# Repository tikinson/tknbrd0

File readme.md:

# tknbrd0

## Intro
### ( !ACHTUNG! work in progress, use by your own risk! )

After a couple of sleepless nights, I decided to get my hands dirty with this sweet and diverse world of mechanical keyboards. As i understood on my way to my current daily driver it's quite interesting challenge. My main idea was to make a cheap keyboard, that can guide me forward in this hobby. 

So, i made a rough sketch of the location of my fingers to understand how far i must go with [ergogen](https://ergogen.xyz/) and then use spacing of switches in KiCad to make a PCB. Also this isn't a bad idea to play around with encoders and small OLED display in my project. As it usually almost everytime happens with first try, i made some mistakes ( learned some lessons :D ) and realize this _after_ i got PCBs from manufacturer. It's not critical, but in some points it could be just unexpectable for those, who would repeat my project. 

By the way here is PCBs appearance:

 WPM and remix of [bongo cat animation](https://www.reddit.com/r/olkb/comments/h00a8b/i_made_an_oled_animation_of_bongo_cat_that/) is showing on my OLED (of course with picture of my cat instead of original one!). With encoders i can scroll my feed, and also fast forward/backward the YouTube videos by 5 seconds. Encoders is very interesting feature in keyboards and detailed explanation of this you can check in [QMK Docs](https://docs.qmk.fm/features/encoders).

 #### important note: in first version of my schematics, unfortunately, encoders works not so stable as expected... sometimes for correct working keyboard must be rebooted.

## Keymap

My keyboard has a 42 keys, and it planned to use with QWERTY layout. For me is also iportant to have access to ukrainian letter Ґ, Ї, and some umlaut letters
Ä, Ö, Ü. I have now a laptop with QWERTZ layout, so have a keyboard with comfortable QWERTY is must have for me. So here is the keymap:

## Case

In file 'path_for400x300.svg' in this repo you can find a complete graphical outline for lasercutted case. I used a 3 mm acrylic sheet and laser in local FabLab.

## Firmware 

I created a fork of QMK firmware [here](https://github.com/tikinson/qmk_firmware) and [here](https://github.com/tikinson/qmk_firmware/tree/master/keyboards/tknbrd/tknbrd0) is tknbrd0 is located inside of QMK fork.

So you can compile firmware from fork or you can find binaries in 'FW' directory of this repo.

## Some important notes

1. Footprint for OLED is mirrored, so i use wires and simple pair of acrylic pieces to hold it with glue (really not a clearest design decision, but it just a first experience, so when it works it works).
2. Case: it's very important to solder RPI Pico a bit higher that it could be to prevent collision with acrylic case!!!
3. Encoders may have strange behaviour because they are connected to one pin. it was a bad decision and when reset keyboard isn't working i just rotate them together for first and then separately, so after this magical manipulation they works as usual.

## BOM (Bill of materials)

Interactive BOM could be handy in assembling process and you can find it [here](/bom/ibom.html)

| Designator       | Footprint                                                        | Quantity | Value                 | LCSC Part #      |
|------------------|------------------------------------------------------------------|----------|-----------------------|------------------|
| D1 - D42         | Diode_SOD-123                                                   | 42       | Diode                 |C83528              |
| EXSW1, EXSW2     | RotaryEncoder_Alps_EC11E-Switch_Vertical_H20mm_CircularMountingHoles | 2        | RotaryEncoder_Switch   |C1322543         |
| J1               | OLED_128x64 (I2C version)                                       | 1        | Conn_01x04            |                  |
| S1 - S42         | MX_PCB_1.00u                                                    | 42       | Keyswitch             |                  |
| U1               | Raspberry_Pi_Pico                                               | 1        | Raspberry_Pi_Pico     |                  |
| rD1              | D_SOD-523                                                       | 1        | 1N4148WT              | C232841          |
| rLED1 - rLED42    | YS-SK6812MINI-E-withCUTOUT                                     | 42       | YS-SK6812MINI-E       |C5149201          |
| aluminum spacer M2(standoff)    |MountingHole_4.3mm_M4_ISO14580                    | 8        | standoff              |                  |

Lasercutting, Knob, Switches all this you can easily find on market on your personal preferences. All that included in BOM is recommended, only LED is optional.

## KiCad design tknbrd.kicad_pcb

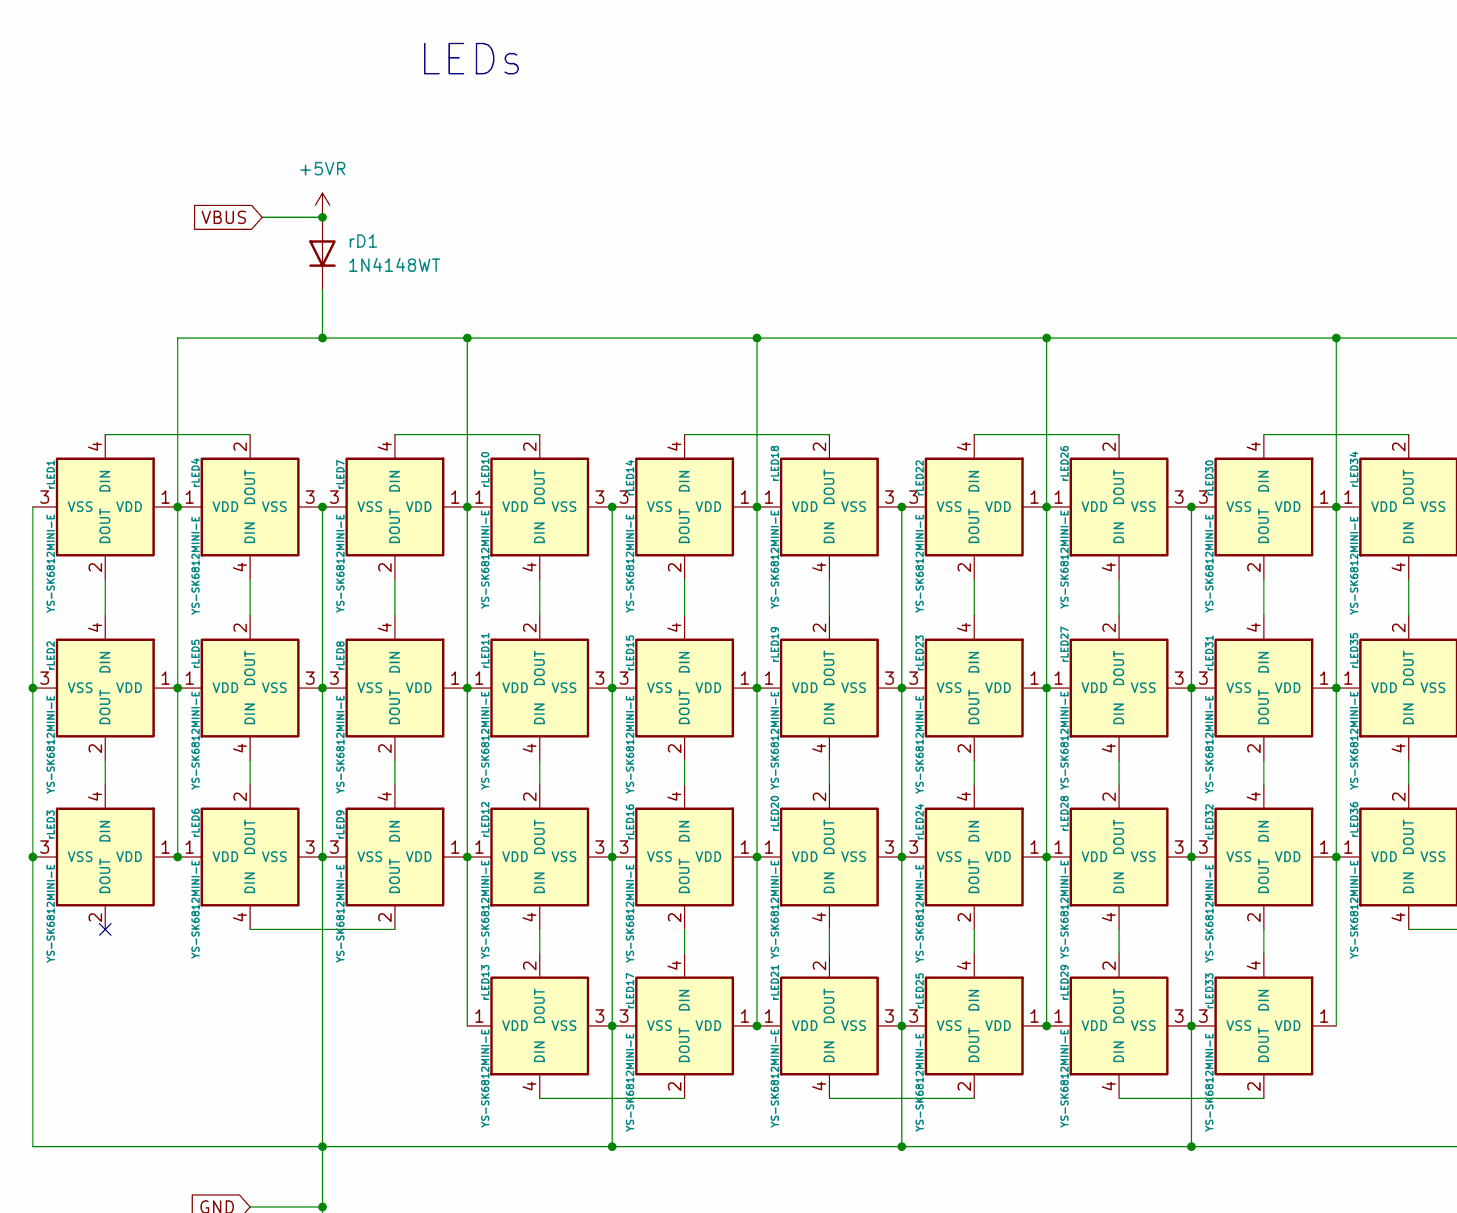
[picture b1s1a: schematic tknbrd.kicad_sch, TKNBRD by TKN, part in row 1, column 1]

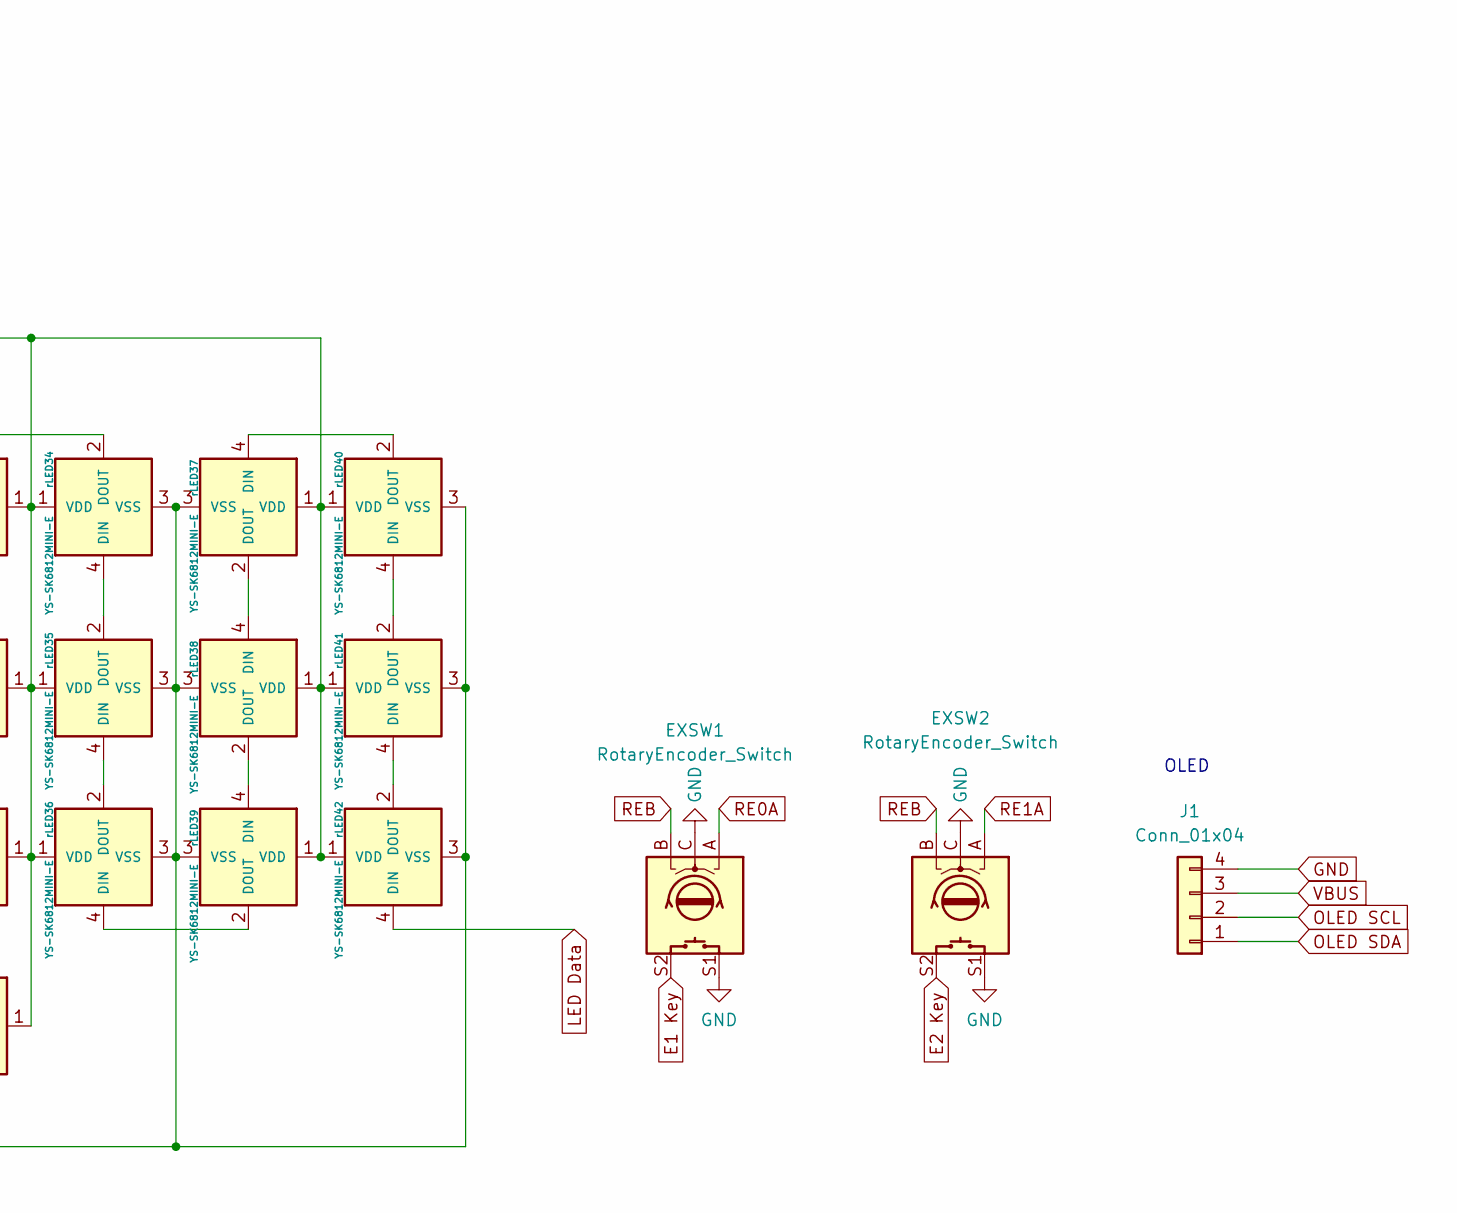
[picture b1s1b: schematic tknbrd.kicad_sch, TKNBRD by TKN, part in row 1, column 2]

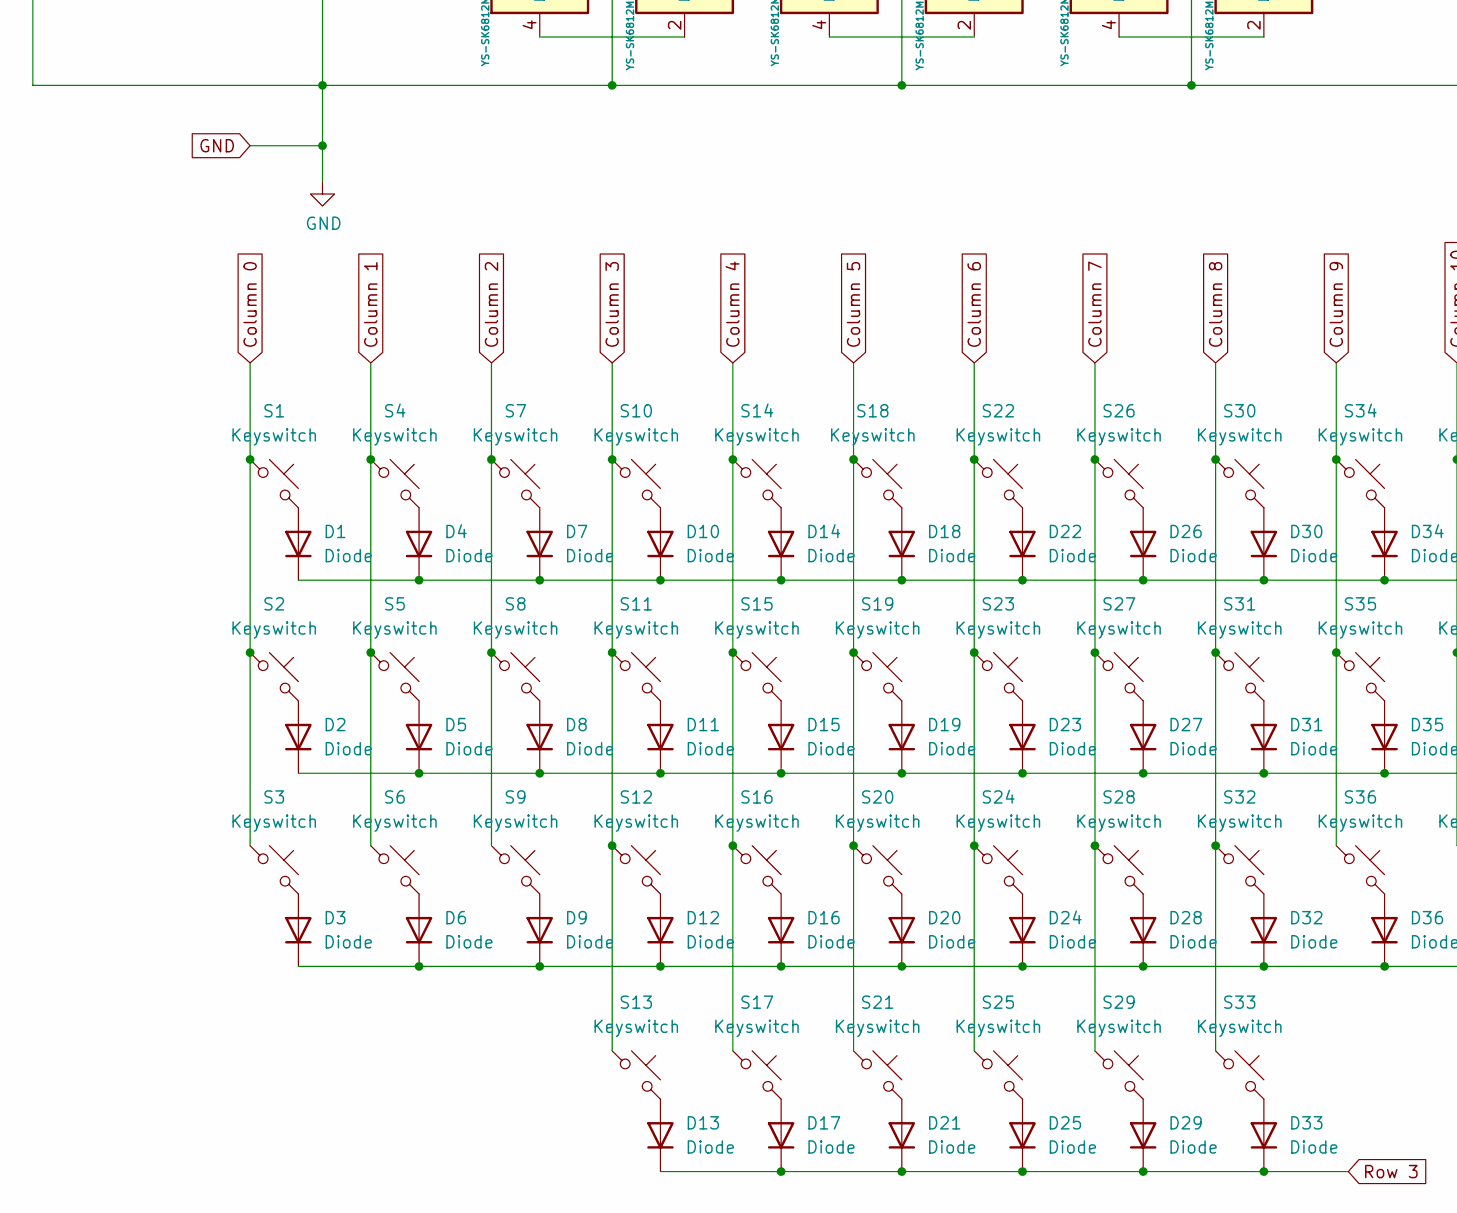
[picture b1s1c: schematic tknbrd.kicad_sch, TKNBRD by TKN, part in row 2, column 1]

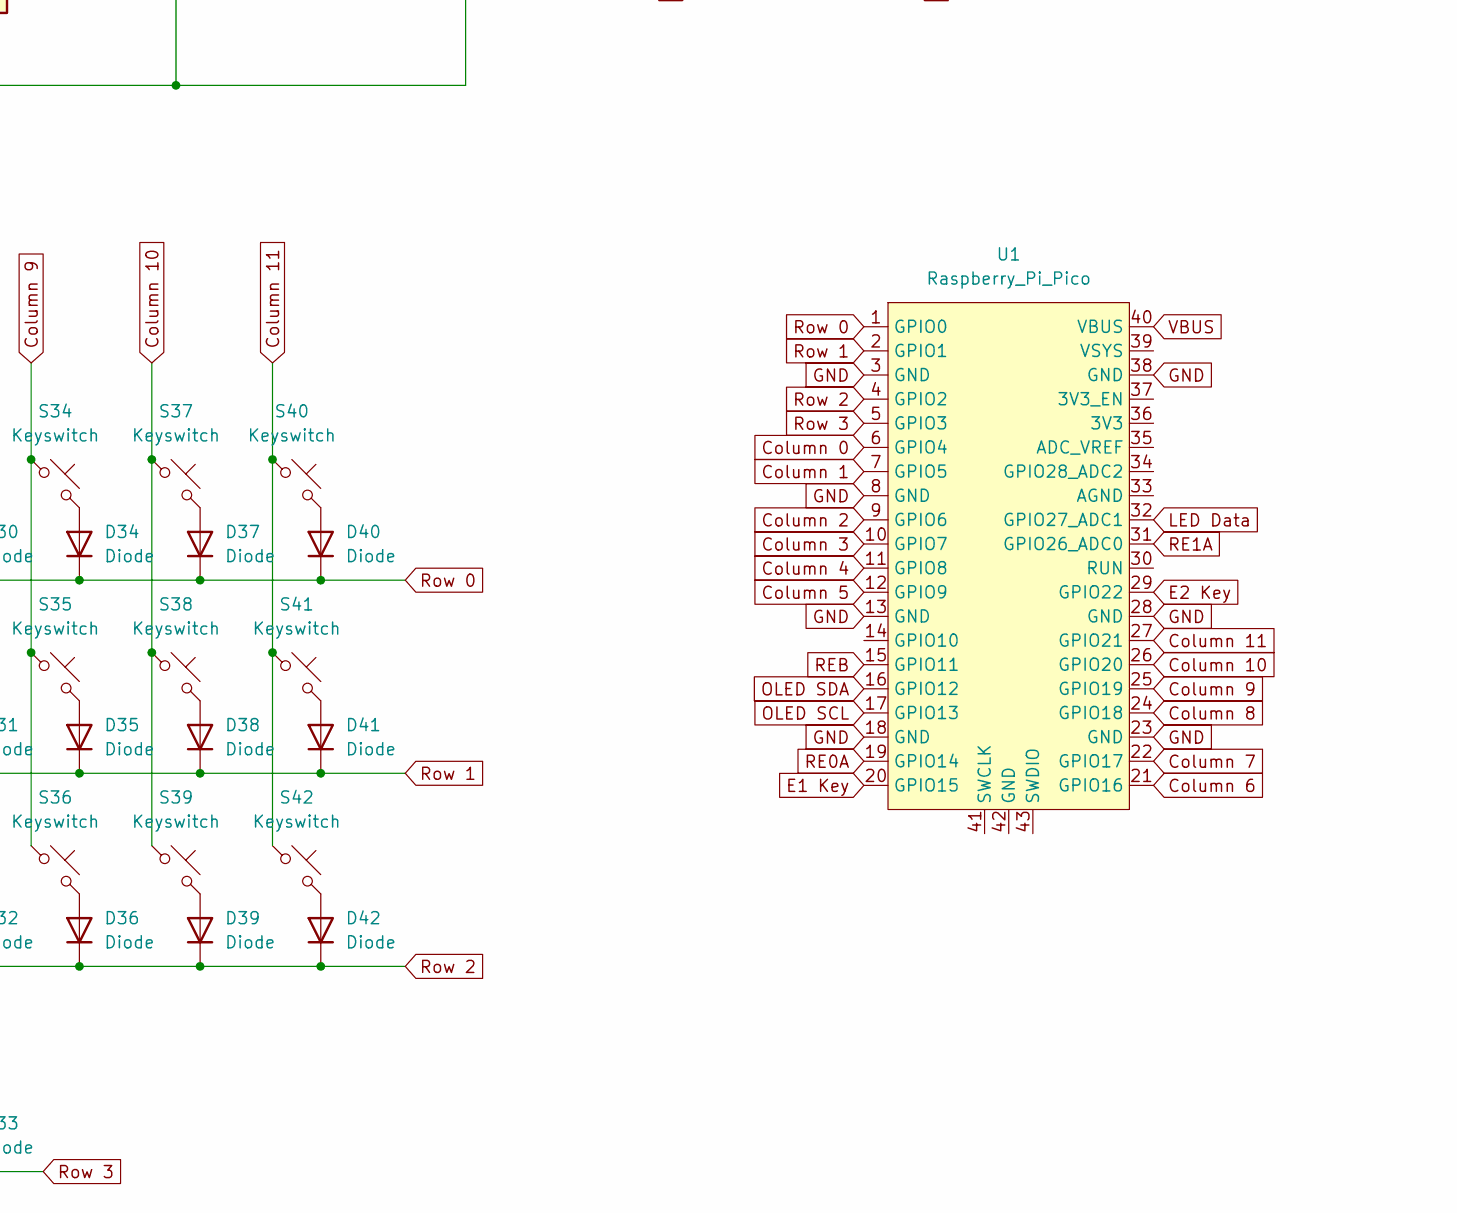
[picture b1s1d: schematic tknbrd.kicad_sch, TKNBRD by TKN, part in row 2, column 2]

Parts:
D1, D2, D3, D4, D5, D6, D7, D8, D9, D10, D11, D12, D13, D14, D15, D16, D17, D18, D19, D20, D21, D22, D23, D24, D25, D26, D27, D28, D29, D30, D31, D32, D33, D34, D35, D36, D37, D38, D39, D40, D41, D42: Diode; Diode_SOD-123
EXSW1, EXSW2: RotaryEncoder_Switch; RotaryEncoder_Alps_EC11E-Switch_Vertical_H20mm_CircularMoun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
J1: Conn_01x04; OLED_128x64
S1, S2, S3, S4, S5, S6, S7, S8, S9, S10, S11, S12, S13, S14, S15, S16, S17, S18, S19, S20, S21, S22, S23, S24, S25, S26, S27, S28, S29, S30, S31, S32, S33, S34, S35, S36, S37, S38, S39, S40, S41, S42: Keyswitch; MX_PCB_1.00u
U1: Raspberry_Pi_Pico
rD1: 1N4148WT; D_SOD-523; JLCPCB Part # C232841
rLED1, rLED2, rLED3, rLED4, rLED5, rLED6, rLED7, rLED8, rLED9, rLED10, rLED11, rLED12, rLED13, rLED14, rLED15, rLED16, rLED17, rLED18, rLED19, rLED20, rLED21, rLED22, rLED23, rLED24, rLED25, rLED26, rLED27, rLED28, rLED29, rLED30, rLED31, rLED32, rLED33, rLED34, rLED35, rLED36, rLED37, rLED38, rLED39, rLED40, rLED41, rLED42: YS-SK6812MINI-E; YS-SK6812MINI-E-withCUTOUT

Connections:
Column 0: S1.1, S2.1, S3.1, U1.6 (GPIO4)
Column 1: S4.1, S5.1, S6.1, U1.7 (GPIO5)
Column 2: S7.1, S8.1, S9.1, U1.9 (GPIO6)
Column 3: S10.1, S11.1, S12.1, S13.1, U1.10 (GPIO7)
Column 4: S14.1, S15.1, S16.1, S17.1, U1.11 (GPIO8)
Column 5: S18.1, S19.1, S20.1, S21.1, U1.12 (GPIO9)
Column 6: S22.1, S23.1, S24.1, S25.1, U1.21 (GPIO16)
Column 7: S26.1, S27.1, S28.1, S29.1, U1.22 (GPIO17)
Column 8: S30.1, S31.1, S32.1, S33.1, U1.24 (GPIO18)
Column 9: S34.1, S35.1, S36.1, U1.25 (GPIO19)
Column 10: S37.1, S38.1, S39.1, U1.26 (GPIO20)
Column 11: S40.1, S41.1, S42.1, U1.27 (GPIO21)
E1 Key: EXSW1.S2, U1.20 (GPIO15)
E2 Key: EXSW2.S2, U1.29 (GPIO22)
GND: EXSW1.C, EXSW1.S1, EXSW2.C, EXSW2.S1, J1.4, U1.3 (GND), U1.8 (GND), U1.13 (GND), U1.18 (GND), U1.23 (GND), U1.28 (GND), U1.38 (GND), rLED1.3 (VSS), rLED2.3 (VSS), rLED3.3 (VSS), rLED4.3 (VSS), rLED5.3 (VSS), rLED6.3 (VSS), rLED7.3 (VSS), rLED8.3 (VSS), rLED9.3 (VSS), rLED10.3 (VSS), rLED11.3 (VSS), rLED12.3 (VSS), rLED13.3 (VSS), rLED14.3 (VSS), rLED15.3 (VSS), rLED16.3 (VSS), rLED17.3 (VSS), rLED18.3 (VSS), rLED19.3 (VSS), rLED20.3 (VSS), rLED21.3 (VSS), rLED22.3 (VSS), rLED23.3 (VSS), rLED24.3 (VSS), rLED25.3 (VSS), rLED26.3 (VSS), rLED27.3 (VSS), rLED28.3 (VSS), rLED29.3 (VSS), rLED30.3 (VSS), rLED31.3 (VSS), rLED32.3 (VSS), rLED33.3 (VSS), rLED34.3 (VSS), rLED35.3 (VSS), rLED36.3 (VSS), rLED37.3 (VSS), rLED38.3 (VSS), rLED39.3 (VSS), rLED40.3 (VSS), rLED41.3 (VSS), rLED42.3 (VSS)
LED Data: U1.32 (GPIO27_ADC1), rLED42.4 (DIN)
unnamed: D1.2 (A), S1.2
unnamed: D2.2 (A), S2.2
unnamed: D3.2 (A), S3.2
unnamed: D4.2 (A), S4.2
unnamed: D5.2 (A), S5.2
unnamed: D6.2 (A), S6.2
unnamed: D7.2 (A), S7.2
unnamed: D8.2 (A), S8.2
unnamed: D9.2 (A), S9.2
unnamed: D10.2 (A), S10.2
unnamed: D11.2 (A), S11.2
unnamed: D12.2 (A), S12.2
unnamed: D13.2 (A), S13.2
unnamed: D14.2 (A), S14.2
unnamed: D15.2 (A), S15.2
unnamed: D16.2 (A), S16.2
unnamed: D17.2 (A), S17.2
unnamed: D18.2 (A), S18.2
unnamed: D19.2 (A), S19.2
unnamed: D20.2 (A), S20.2
unnamed: D21.2 (A), S21.2
unnamed: D22.2 (A), S22.2
unnamed: D23.2 (A), S23.2
unnamed: D24.2 (A), S24.2
unnamed: D25.2 (A), S25.2
unnamed: D26.2 (A), S26.2
unnamed: D27.2 (A), S27.2
unnamed: D28.2 (A), S28.2
unnamed: D29.2 (A), S29.2
unnamed: D30.2 (A), S30.2
unnamed: D31.2 (A), S31.2
unnamed: D32.2 (A), S32.2
unnamed: D33.2 (A), S33.2
unnamed: D34.2 (A), S34.2
unnamed: D35.2 (A), S35.2
unnamed: D36.2 (A), S36.2
unnamed: D37.2 (A), S37.2
unnamed: D38.2 (A), S38.2
unnamed: D39.2 (A), S39.2
unnamed: D40.2 (A), S40.2
unnamed: D41.2 (A), S41.2
unnamed: D42.2 (A), S42.2
unnamed: rD1.1 (K), rLED1.1 (VDD), rLED2.1 (VDD), rLED3.1 (VDD), rLED4.1 (VDD), rLED5.1 (VDD), rLED6.1 (VDD), rLED7.1 (VDD), rLED8.1 (VDD), rLED9.1 (VDD), rLED10.1 (VDD), rLED11.1 (VDD), rLED12.1 (VDD), rLED13.1 (VDD), rLED14.1 (VDD), rLED15.1 (VDD), rLED16.1 (VDD), rLED17.1 (VDD), rLED18.1 (VDD), rLED19.1 (VDD), rLED20.1 (VDD), rLED21.1 (VDD), rLED22.1 (VDD), rLED23.1 (VDD), rLED24.1 (VDD), rLED25.1 (VDD), rLED26.1 (VDD), rLED27.1 (VDD), rLED28.1 (VDD), rLED29.1 (VDD), rLED30.1 (VDD), rLED31.1 (VDD), rLED32.1 (VDD), rLED33.1 (VDD), rLED34.1 (VDD), rLED35.1 (VDD), rLED36.1 (VDD), rLED37.1 (VDD), rLED38.1 (VDD), rLED39.1 (VDD), rLED40.1 (VDD), rLED41.1 (VDD), rLED42.1 (VDD)
unnamed: rLED1.4 (DIN), rLED4.2 (DOUT)
unnamed: rLED1.2 (DOUT), rLED2.4 (DIN)
unnamed: rLED2.2 (DOUT), rLED3.4 (DIN)
unnamed: rLED4.4 (DIN), rLED5.2 (DOUT)
unnamed: rLED5.4 (DIN), rLED6.2 (DOUT)
unnamed: rLED6.4 (DIN), rLED9.2 (DOUT)
unnamed: rLED7.2 (DOUT), rLED8.4 (DIN)
unnamed: rLED8.2 (DOUT), rLED9.4 (DIN)
unnamed: rLED10.4 (DIN), rLED11.2 (DOUT)
unnamed: rLED7.4 (DIN), rLED10.2 (DOUT)
unnamed: rLED11.4 (DIN), rLED12.2 (DOUT)
unnamed: rLED12.4 (DIN), rLED13.2 (DOUT)
unnamed: rLED13.4 (DIN), rLED17.2 (DOUT)
unnamed: rLED14.4 (DIN), rLED18.2 (DOUT)
unnamed: rLED14.2 (DOUT), rLED15.4 (DIN)
unnamed: rLED15.2 (DOUT), rLED16.4 (DIN)
unnamed: rLED16.2 (DOUT), rLED17.4 (DIN)
unnamed: rLED18.4 (DIN), rLED19.2 (DOUT)
unnamed: rLED19.4 (DIN), rLED20.2 (DOUT)
unnamed: rLED20.4 (DIN), rLED21.2 (DOUT)
unnamed: rLED21.4 (DIN), rLED25.2 (DOUT)
unnamed: rLED22.4 (DIN), rLED26.2 (DOUT)
unnamed: rLED22.2 (DOUT), rLED23.4 (DIN)
unnamed: rLED23.2 (DOUT), rLED24.4 (DIN)
unnamed: rLED24.2 (DOUT), rLED25.4 (DIN)
unnamed: rLED26.4 (DIN), rLED27.2 (DOUT)
unnamed: rLED27.4 (DIN), rLED28.2 (DOUT)
unnamed: rLED28.4 (DIN), rLED29.2 (DOUT)
unnamed: rLED29.4 (DIN), rLED33.2 (DOUT)
unnamed: rLED30.4 (DIN), rLED34.2 (DOUT)
unnamed: rLED30.2 (DOUT), rLED31.4 (DIN)
unnamed: rLED31.2 (DOUT), rLED32.4 (DIN)
unnamed: rLED32.2 (DOUT), rLED33.4 (DIN)
unnamed: rLED34.4 (DIN), rLED35.2 (DOUT)
unnamed: rLED35.4 (DIN), rLED36.2 (DOUT)
unnamed: rLED36.4 (DIN), rLED39.2 (DOUT)
unnamed: rLED37.4 (DIN), rLED40.2 (DOUT)
unnamed: rLED37.2 (DOUT), rLED38.4 (DIN)
unnamed: rLED38.2 (DOUT), rLED39.4 (DIN)
unnamed: rLED40.4 (DIN), rLED41.2 (DOUT)
unnamed: rLED41.4 (DIN), rLED42.2 (DOUT)
OLED SCL: J1.2, U1.17 (GPIO13)
OLED SDA: J1.1, U1.16 (GPIO12)
RE0A: EXSW1.A, U1.19 (GPIO14)
RE1A: EXSW2.A, U1.31 (GPIO26_ADC0)
REB: EXSW1.B, EXSW2.B, U1.15 (GPIO11)
Row 0: D1.1 (K), D4.1 (K), D7.1 (K), D10.1 (K), D14.1 (K), D18.1 (K), D22.1 (K), D26.1 (K), D30.1 (K), D34.1 (K), D37.1 (K), D40.1 (K), U1.1 (GPIO0)
Row 1: D2.1 (K), D5.1 (K), D8.1 (K), D11.1 (K), D15.1 (K), D19.1 (K), D23.1 (K), D27.1 (K), D31.1 (K), D35.1 (K), D38.1 (K), D41.1 (K), U1.2 (GPIO1)
Row 2: D3.1 (K), D6.1 (K), D9.1 (K), D12.1 (K), D16.1 (K), D20.1 (K), D24.1 (K), D28.1 (K), D32.1 (K), D36.1 (K), D39.1 (K), D42.1 (K), U1.4 (GPIO2)
Row 3: D13.1 (K), D17.1 (K), D21.1 (K), D25.1 (K), D29.1 (K), D33.1 (K), U1.5 (GPIO3)
VBUS: J1.3, U1.40 (VBUS), rD1.2 (A)

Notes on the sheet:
OLED
LEDs

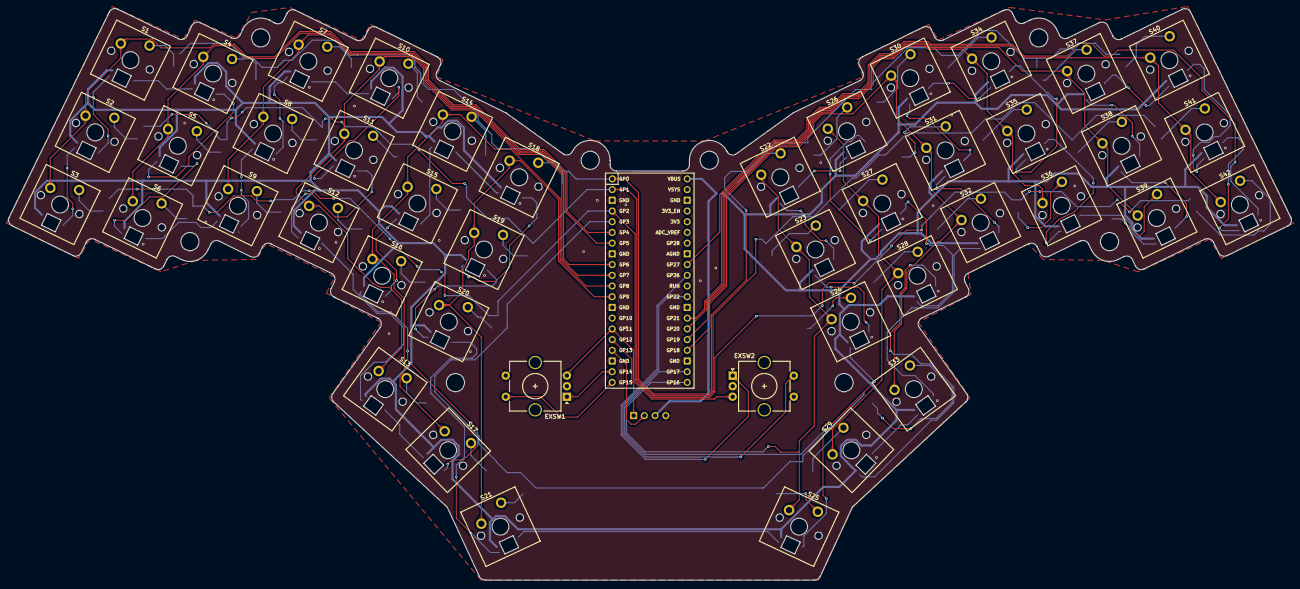
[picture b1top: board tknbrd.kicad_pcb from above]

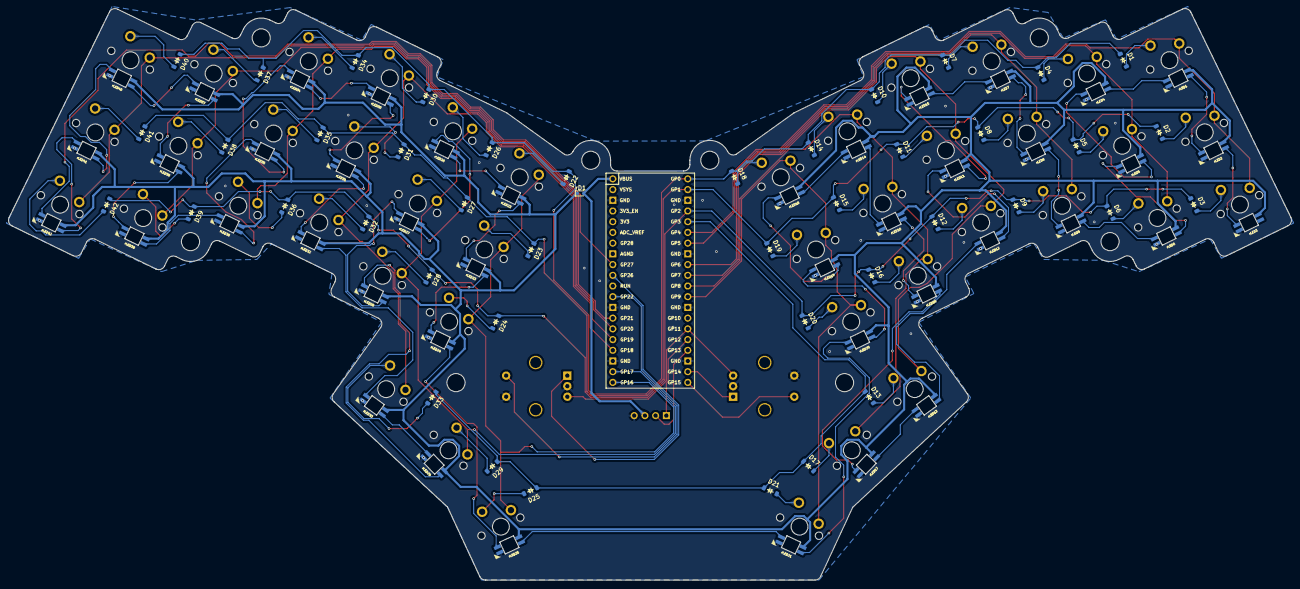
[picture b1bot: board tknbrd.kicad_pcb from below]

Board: 2 copper layers, 304.1 x 135.4 mm, 131 parts (43 on the bottom side), 110 nets.

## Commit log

2024-09-29 add a project in current state
2024-09-29 readme upd
2024-09-30 typos typos
2024-12-19 ibom
